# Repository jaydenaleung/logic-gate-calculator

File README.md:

Logic Gate Calculator
=====

A custom calculator on a printed circuit board (PCB), made entirely from logic gates. The calculator takes in any number of inputs from 0-9 and can output their sum (up to 9).
-----

**Hours Spent:** 20

## Overview

*Logic Gate Calculator (LGC)* is a PCB that employs multiple buttons, each mapped to a digit 0-9, and sums them when pressed. This sum is shown by lighting up an LED mapped to a specific output 0-9. The PCB is powered by a 5-12V and a ground pin, regulated to 5V. I hand-soldered all the through-hole components myself!

## Why I Did This Project

This project began as an assignment for the prerequisite course to the **2026 MIT BeaverWorks Basics of ASICs** program. Since I did also that course the year before, I wanted to go further with the assignments. I took our material on logic gates to the max and decided to build a simple calculator from scratch, for which I did some extra research on adders/half-adders. This was just a fun little project! I really learned a lot about the fine complexities of computing.

## Background

To lock in the theory, I first built every logic gate from bare transistors. I used those logic gates to build the adders and the binary/decimal encoders/decoders for the calculator. 

In the end, I came up with a pipeline that: 
1. **Takes in** inputs from push-buttons (corresponding to digits 0-9)
2. **Encodes** them into binary using the Texas Instruments 74HC147 denary to binary IC
3. **Inverts** the numbers (0 -> 1, 1 -> 0) due to the encoder's active-low nature, using the TI 74HC04 inverter IC
4. **Adds** the binary values using the TI 74HC283 adder 4-bit adder
5. **Decodes** the binary values into decimal outputs (up to 9) using the TI 74HC42 binary to denary IC
6. **Activates** LEDs corresponding to the output digit (0-9)

## Key Lessons

Initially, after soldering the components onto the entire PCB, I could not figure out why the voltage fluctuated randomly where it was supposed to be 5V. I suspected that an **unconnected ground was picking up electrical noise** or the **voltage regulator was fried from an accidental short**, I resoldered the entire board - only to find out that the issue was **electrostatic discharge (ESD)**. (This is why I am wearing rubber gloves in the demo.) I learned that the L7805 linear regulator and other widely-used ICs can be **generally resilient** to low-voltage, quick shorts and that ESD is a larger issue when **handling PCBs**.

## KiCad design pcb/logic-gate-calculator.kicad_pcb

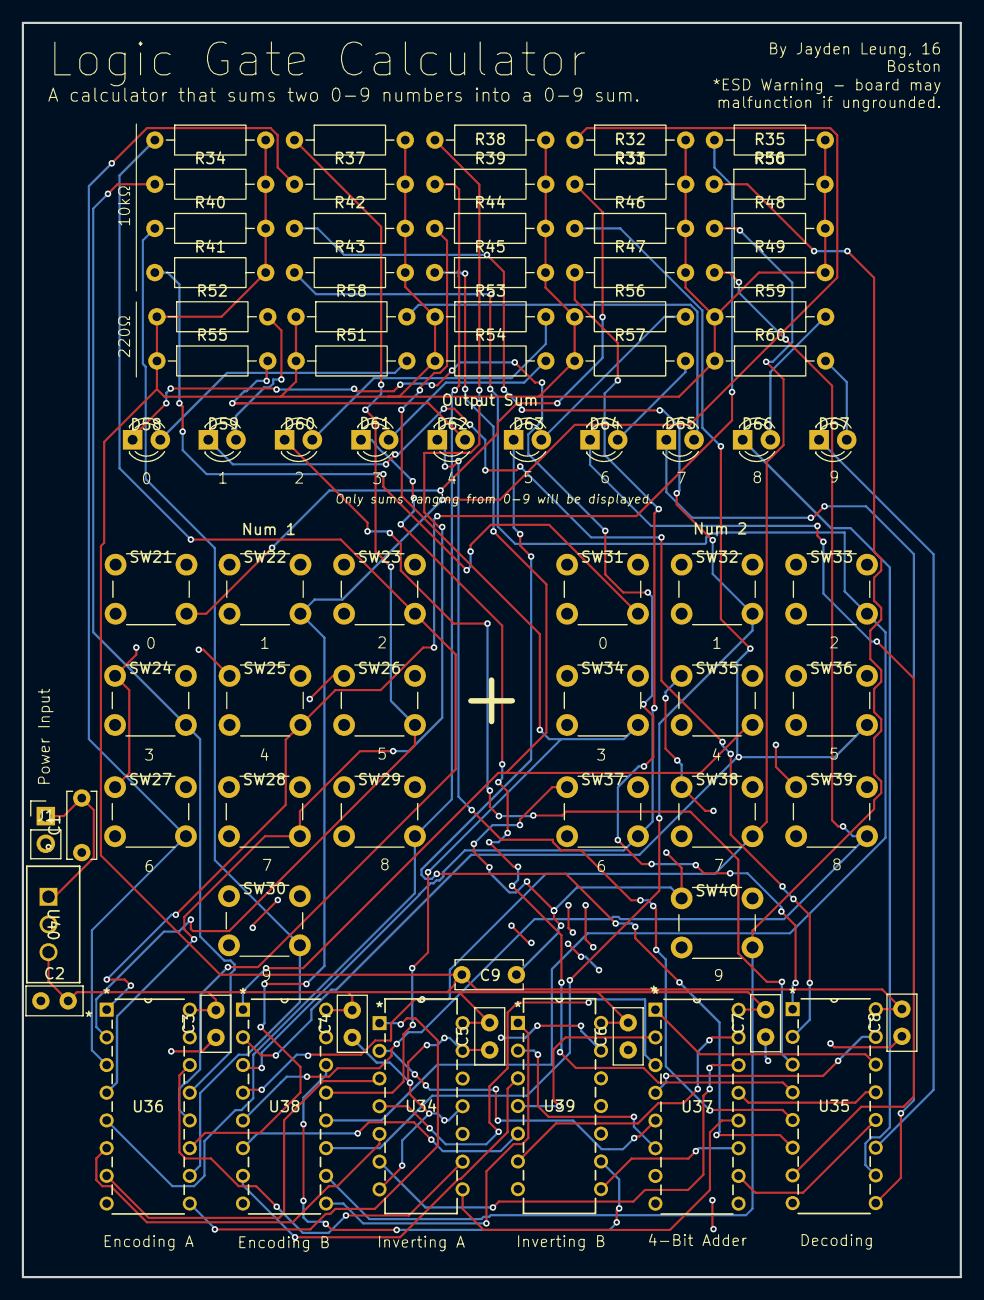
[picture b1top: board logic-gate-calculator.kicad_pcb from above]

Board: 2 copper layers, 86.0 x 115.0 mm, 77 parts (0 on the bottom side), 63 nets.

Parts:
C1, C9: 2.2µF; C_Disc_D6.0mm_W2.5mm_P5.00mm
C2, C3, C4, C5, C6, C7, C8: 0.1µF; C_Disc_D5.0mm_W2.5mm_P2.50mm
D58, D59, D60, D61, D62, D63, D64, D65, D66, D67: LED; LED_D3.0mm
J1: Power_Dupont_Socket_Connector; PinHeader_1x02_P2.54mm_Vertical
R31, R32, R33, R34, R35, R36, R37, R38, R39, R40, R41, R42, R43, R44, R45, R46, R47, R48, R49, R50: 10kΩ; R_Axial_DIN0207_L6.3mm_D2.5mm_P10.16mm_Horizontal
R51, R52, R53, R54, R55, R56, R57, R58, R59, R60: 220Ω; R_Axial_DIN0207_L6.3mm_D2.5mm_P10.16mm_Horizontal
SW21: SW_0_in_A; SW_PUSH_6mm
SW22: SW_1_in_A; SW_PUSH_6mm
SW23: SW_2_in_A; SW_PUSH_6mm
SW24: SW_3_in_A; SW_PUSH_6mm
SW25: SW_4_in_A; SW_PUSH_6mm
SW26: SW_5_in_A; SW_PUSH_6mm
SW27: SW_6_in_A; SW_PUSH_6mm
SW28: SW_7_in_A; SW_PUSH_6mm
SW29: SW_8_in_A; SW_PUSH_6mm
SW30: SW_9_in_A; SW_PUSH_6mm
SW31: SW_0_in_B; SW_PUSH_6mm
SW32: SW_1_in_B; SW_PUSH_6mm
SW33: SW_2_in_B; SW_PUSH_6mm
SW34: SW_3_in_B; SW_PUSH_6mm
SW35: SW_4_in_B; SW_PUSH_6mm
SW36: SW_5_in_B; SW_PUSH_6mm
SW37: SW_6_in_B; SW_PUSH_6mm
SW38: SW_7_in_B; SW_PUSH_6mm
SW39: SW_8_in_B; SW_PUSH_6mm
SW40: SW_9_in_B; SW_PUSH_6mm
U34, U39: N14; SN74HC04N
U35: N16; SN74HC42N
U36, U38: N16; CD74HC147E
U37: N16; CD74HC283E
U40: L7805; L7805CV

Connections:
0_in_A: R31.1, SW21.4
0_in_B: R41.1, SW31.4
0_out: C1.1, C2.1, C3.1, C4.1, C5.1, C6.1, C7.1, C8.1, C9.2, J1.2, SW21.1, SW22.1, SW23.1, SW24.1, SW25.1, SW26.1, SW27.1, SW28.1, SW29.1, SW30.1, SW31.1, SW32.1, SW33.1, SW34.1, SW35.1, SW36.1, SW37.1, SW38.1, SW39.1, SW40.1, U34.7 (GND), U34.11 (5A), U34.13 (6A), U35.8 (GND), U36.8 (GND), U37.7 (CIN), U37.8 (GND), U38.8 (GND), U39.7 (GND), U39.11 (5A), U39.13 (6A), U40.2 (GND)
00_out_A_AH: U34.4 (2Y), U37.3 (A1)
0_out_A_AH: U34.2 (1Y), U37.5 (A0)
0000_out_A_AH: U34.8 (4Y), U37.12 (A3)
000_out_A_AH: U34.6 (3Y), U37.14 (A2)
0_out_A_AL: U34.1 (1A), U36.9 (*Y0)
00_out_A_AL: U34.3 (2A), U36.7 (*Y1)
000_out_A_AL: U34.5 (3A), U36.6 (*Y2)
0000_out_A_AL: U34.9 (4A), U36.14 (*Y3)
00_out_B_AH: U37.2 (B1), U39.4 (2Y)
0_out_B_AH: U37.6 (B0), U39.2 (1Y)
0000_out_B_AH: U37.11 (B3), U39.8 (4Y)
000_out_B_AH: U37.15 (B2), U39.6 (3Y)
0_out_B_AL: U38.9 (*Y0), U39.1 (1A)
00_out_B_AL: U38.7 (*Y1), U39.3 (2A)
000_out_B_AL: U38.6 (*Y2), U39.5 (3A)
0000_out_B_AL: U38.14 (*Y3), U39.9 (4A)
1_in_A: R32.1, SW22.4, U36.11 (*I1)
1_in_B: R42.1, SW32.4, U38.11 (*I1)
2_in_A: R33.1, SW23.4, U36.12 (*I2)
2_in_B: R43.1, SW33.4, U38.12 (*I2)
3_in_A: R34.1, SW24.4, U36.13 (*I3)
3_in_B: R44.1, SW34.4, U38.13 (*I3)
4_in_A: R35.1, SW25.4, U36.1 (*I4)
4_in_B: R45.1, SW35.4, U38.1 (*I4)
5_in_A: R36.1, SW26.4, U36.2 (*I5)
5_in_B: R46.1, SW36.4, U38.2 (*I5)
6_in_A: R37.1, SW27.4, U36.3 (*I6)
6_in_B: R47.1, SW37.4, U38.3 (*I6)
7_in_A: R38.1, SW28.4, U36.4 (*I7)
7_in_B: R48.1, SW38.4, U38.4 (*I7)
8_in_A: R39.1, SW29.4, U36.5 (*I8)
8_in_B: R49.1, SW39.4, U38.5 (*I8)
9_in_A: R40.1, SW30.4, U36.10 (*I9)
9_in_B: R50.1, SW40.4, U38.10 (*I9)
+5V: C2.2, C3.2, C4.2, C5.2, C6.2, C7.2, C8.2, C9.1, R31.2, R32.2, R33.2, R34.2, R35.2, R36.2, R37.2, R38.2, R39.2, R40.2, R41.2, R42.2, R43.2, R44.2, R45.2, R46.2, R47.2, R48.2, R49.2, R50.2, R51.1, R52.1, R53.1, R54.1, R55.1, R56.1, R57.1, R58.1, R59.1, R60.1, U34.14 (VCC), U35.16 (VCC), U36.16 (VCC), U37.16 (VCC), U38.16 (VCC), U39.14 (VCC), U40.3 (OUT)
+PWR_OUTPUT: C1.2, J1.1, U40.1 (IN)
LED_0: D58.1 (K), U35.1 (0)
LED_1: D59.1 (K), U35.2 (1)
LED_2: D60.1 (K), U35.3 (2)
LED_3: D61.1 (K), U35.4 (3)
LED_4: D62.1 (K), U35.5 (4)
LED_5: D63.1 (K), U35.6 (5)
LED_6: D64.1 (K), U35.7 (6)
LED_7: D65.1 (K), U35.9 (7)
LED_8: D66.1 (K), U35.10 (8)
LED_9: D67.1 (K), U35.11 (9)
unnamed: D58.2 (A), R51.2
unnamed: D59.2 (A), R52.2
unnamed: D60.2 (A), R53.2
unnamed: D61.2 (A), R54.2
unnamed: D62.2 (A), R55.2
unnamed: D63.2 (A), R56.2
unnamed: D64.2 (A), R57.2
unnamed: D65.2 (A), R58.2
unnamed: D66.2 (A), R59.2
unnamed: D67.2 (A), R60.2
SUM_0000: U35.12 (D), U37.10 (S3)
SUM_000: U35.13 (C), U37.13 (S2)
SUM_00: U35.14 (B), U37.1 (S1)
SUM_0: U35.15 (A), U37.4 (S0)

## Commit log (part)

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2026-03-24 Finish schematic except arduino interface
2026-03-28 finish pcb and upload gerbers and step
